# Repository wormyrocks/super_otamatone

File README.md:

# super_otamatone

Because the world needs a better Otamatone.

In order to set up build environment, you must have three .mk files from the Arduino Makefile repository in arduino/build_scripts

Teensy.mk
Common.mk
Arduino.mk

https://github.com/sudar/Arduino-Makefile

Running setup.sh in that directory should download them automatically.
You also need the Arduino application and Teensyduino, as well as the libraries specified in the Makefile.

This library uses my fork of the arduino-menusystem library, which can be found here.
https://github.com/wormyrocks/arduino-menusystem

It is included as a submodule.

'upload' script automates compilation, upload, and opening the serial monitor.

The last two require the tyc program. Find binaries here. https://github.com/Koromix/ty/releases
tyc should also be in /arduino/otamatone.

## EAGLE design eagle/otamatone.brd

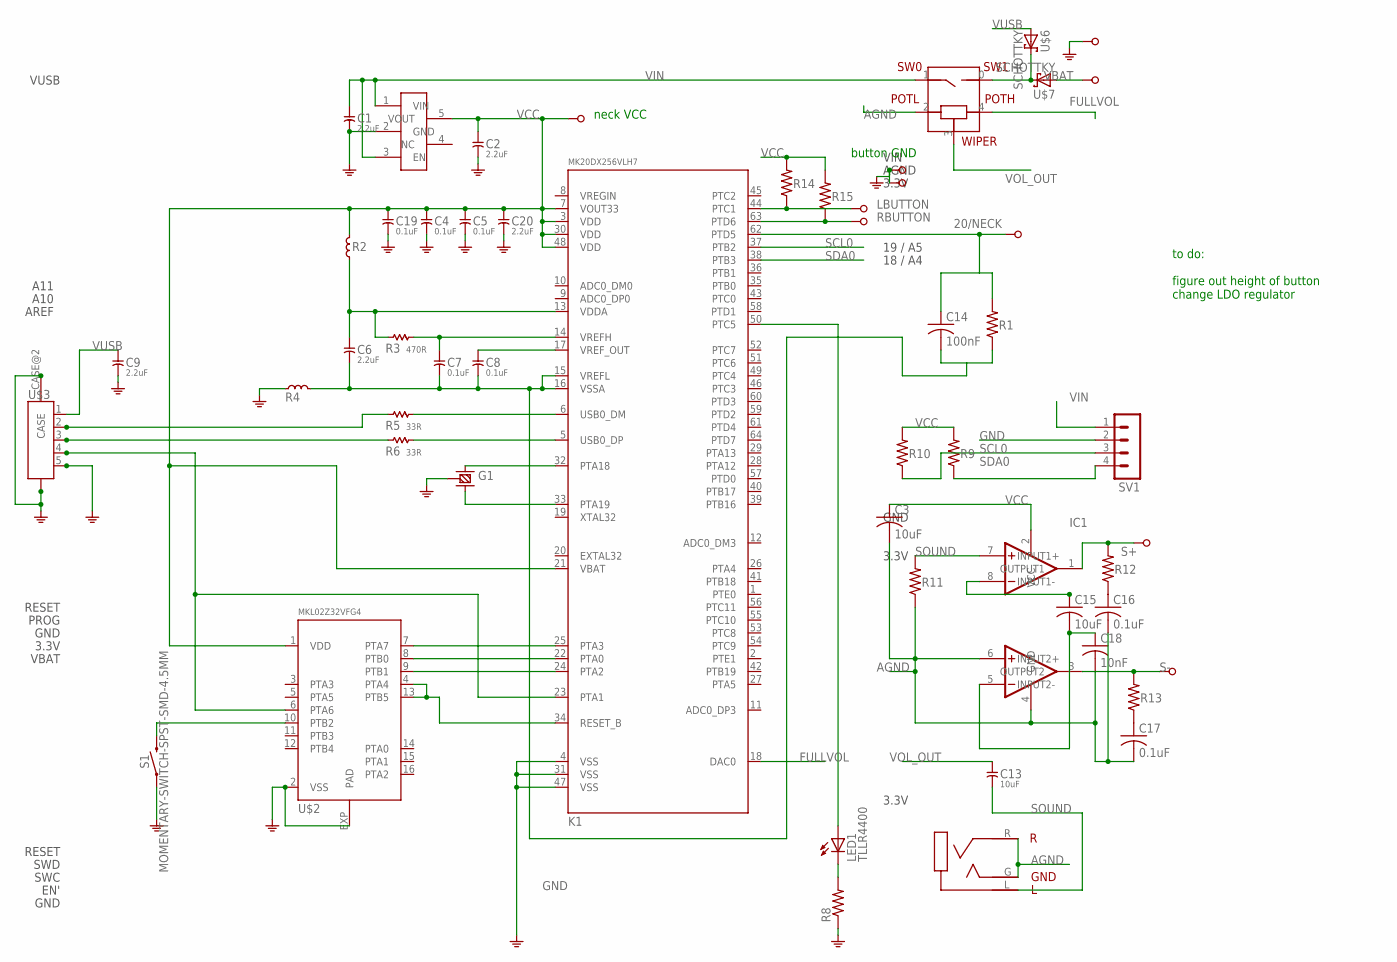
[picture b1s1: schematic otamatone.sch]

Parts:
B+: PIN; PTH_39MIL
B-: PIN; PTH_39MIL
C1, C2, C6, C9, C20: 2.2uF; C0603
C3, C13, C15: 10uF; C0603
C4, C5, C7, C8, C19: 0.1uF; C0402
C14: 100nF; C0402
C16, C17: 0.1uF; C0603
C18: 10nF; C0603
G1: CRYSTAL-; CRYS
IC1: TDA2822MSOP8; SOP8
K1: MK20DX256VLH7; LQFP64-05
LED1: TLLR4400; LED3MM
R1: 62K; R0402
R2, R4: FERRITE; L0603
R3: 470R; R0402
R5, R6: 33R; R0402
R8: R-US_R0603; R0603
R9, R10, R14, R15: 10K; R0402
R11: 10K; R0603
R12, R13: 4.7; R0603
S1: MOMENTARY-SWITCH-SPST-SMD-4.5MM; TACTILE_SWITCH_SMD_4.5MM
S+: PINSMT; SMD
S-: PINSMT; SMD
SV1: MA04-1
SX1, SX2, SX3, SX4: PIN; PTH_39MIL
U$1: P170S; 5PIN_POT
U$2: MKL02Z32VFG4; QFN16
U$3: VERT_USB; TALL_BOI
U$4: VERT_JACK; AUDIOJACK
U$5: AP2112K; SOT25
U$6, U$7: SCHOTTKY; LED-0805
Z+: PINSMT; SMD
Z-: PINSMT; SMD

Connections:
20/NECK: C14.1, K1.62 (PTD5), R1.2, Z-.P$1
AGND: C3.2, C6.2, C7.2, C8.2, C14.2, C16.2, C17.2, C18.2, IC1.4 (GND), IC1.6 (INPUT2+), K1.15 (VREFL), K1.16 (VSSA), R1.1, R4.2, R11.1, U$1.2 (POTL), U$4.G (GND), U$4.R
FULLVOL: K1.18 (DAC0), U$1.4 (POTH)
GND: B-.1, C1.2, C2.2, C4.2, C5.2, C9.2, C19.2, C20.2, G1.P$1 (GND), G1.P$4 (GND), K1.4 (VSS), K1.31 (VSS), K1.47 (VSS), R4.1, R8.1, S1.2 (1), S1.3 (1), SV1.2, SX1.1, SX3.1, U$2.2 (VSS), U$2.EXP (PAD), U$3.5, U$3.CASE, U$3.CASE@2 (CASE), U$5.2 (GND)
LBUTTON: K1.44 (PTC1), R14.1, SX2.1
unnamed: U$1.0 (SW1), U$6.- (C), U$7.- (C)
unnamed: K1.22 (PTA0), U$2.8 (PTB0)
unnamed: K1.24 (PTA2), U$2.9 (PTB1)
unnamed: G1.P$2 (1), K1.32 (PTA18)
unnamed: G1.P$3 (2), K1.33 (PTA19)
unnamed: C15.1, IC1.8 (INPUT1-)
unnamed: K1.25 (PTA3), U$2.7 (PTA7)
unnamed: S1.1 (2), S1.4 (2), U$2.10 (PTB2)
unnamed: C8.1, K1.17 (VREF_OUT)
unnamed: K1.34 (RESET_B), U$2.4 (PTA4), U$2.13 (PTB5)
unnamed: C7.1, K1.14 (VREFH), R3.2
unnamed: C6.1, K1.13 (VDDA), R2.1, R3.1
unnamed: C16.1, R12.1
unnamed: K1.23 (PTA1), U$2.6 (PTA6), U$3.4
unnamed: C17.1, R13.1
unnamed: C15.2, C18.1, IC1.5 (INPUT2-)
unnamed: K1.50 (PTC5), LED1.A
unnamed: LED1.K (C), R8.2
RBUTTON: K1.63 (PTD6), R15.1, SX4.1
S+: IC1.1 (OUTPUT1), R12.2, S+.P$1
S-: IC1.3 (OUTPUT2), R13.2, S-.P$1
SCL0: K1.37 (PTB2), R10.1, SV1.3
SDA0: K1.38 (PTB3), R9.1, SV1.4
SOUND: C13.2, IC1.7 (INPUT1+), R11.2, U$4.L
USB0_DM: K1.6 (USB0_DM), R5.2
USB0_DP: K1.5 (USB0_DP), R6.2
USB_M: R5.1, U$3.2
USB_P: R6.1, U$3.3
VBAT: B+.1, U$7.+ (A)
VCC: C2.1, C3.1, C4.1, C5.1, C19.1, C20.1, IC1.2 (VCC), K1.3 (VDD), K1.7 (VOUT33), K1.21 (VBAT), K1.30 (VDD), K1.48 (VDD), R2.2, R9.2, R10.2, R14.2, R15.2, U$2.1 (VDD), U$5.5 (VOUT), Z+.P$1
VIN: C1.1, SV1.1, U$1.1 (SW0), U$5.1 (VIN), U$5.3 (EN)
VOL_OUT: C13.1, U$1.3 (WIPER)
VUSB: C9.1, U$3.1, U$6.+ (A)

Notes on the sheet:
VIN
AGND
3.3V
19 / A5
18 / A4
GND
VBAT
RESET
PROG
A11
A10
AREF
VUSB
SWD
SWC
EN'
to do: figure out height of button change LDO regulator
neck VCC
button GND

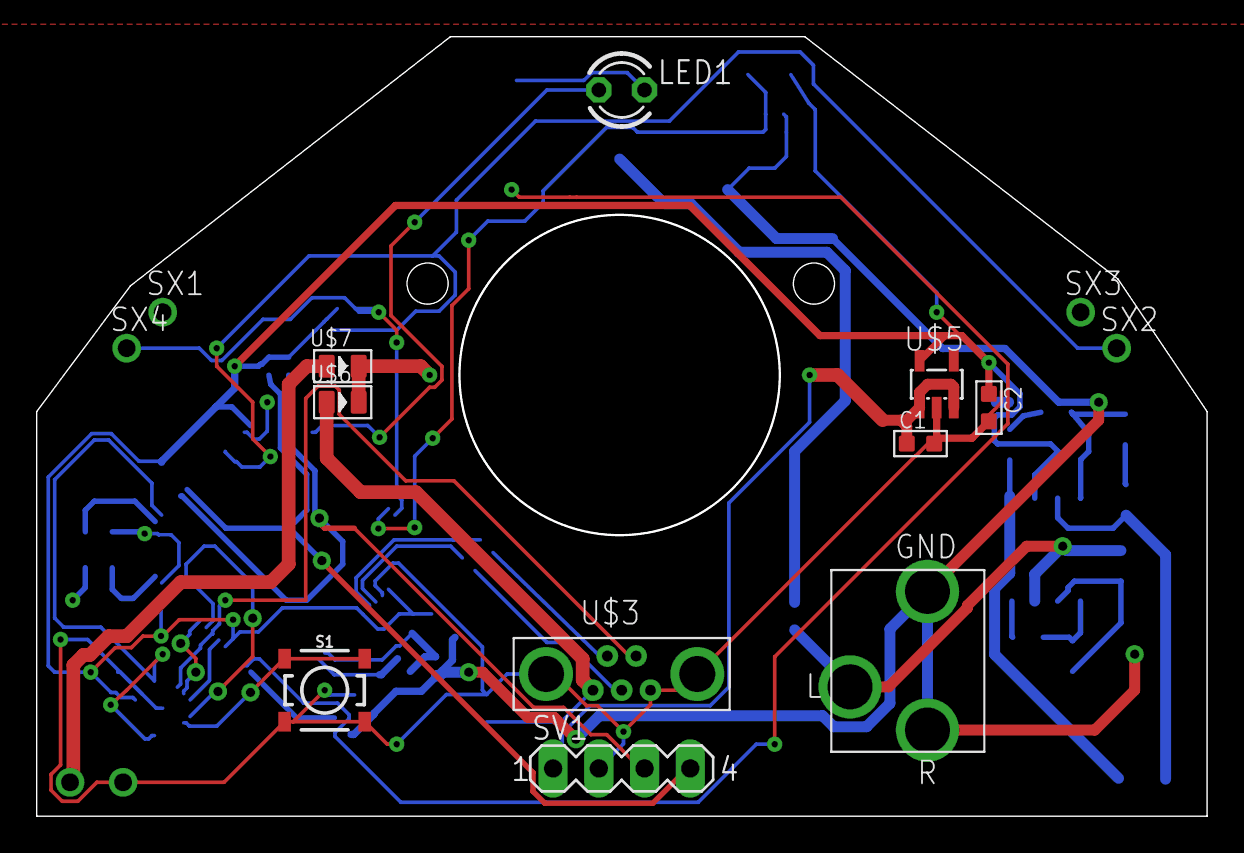
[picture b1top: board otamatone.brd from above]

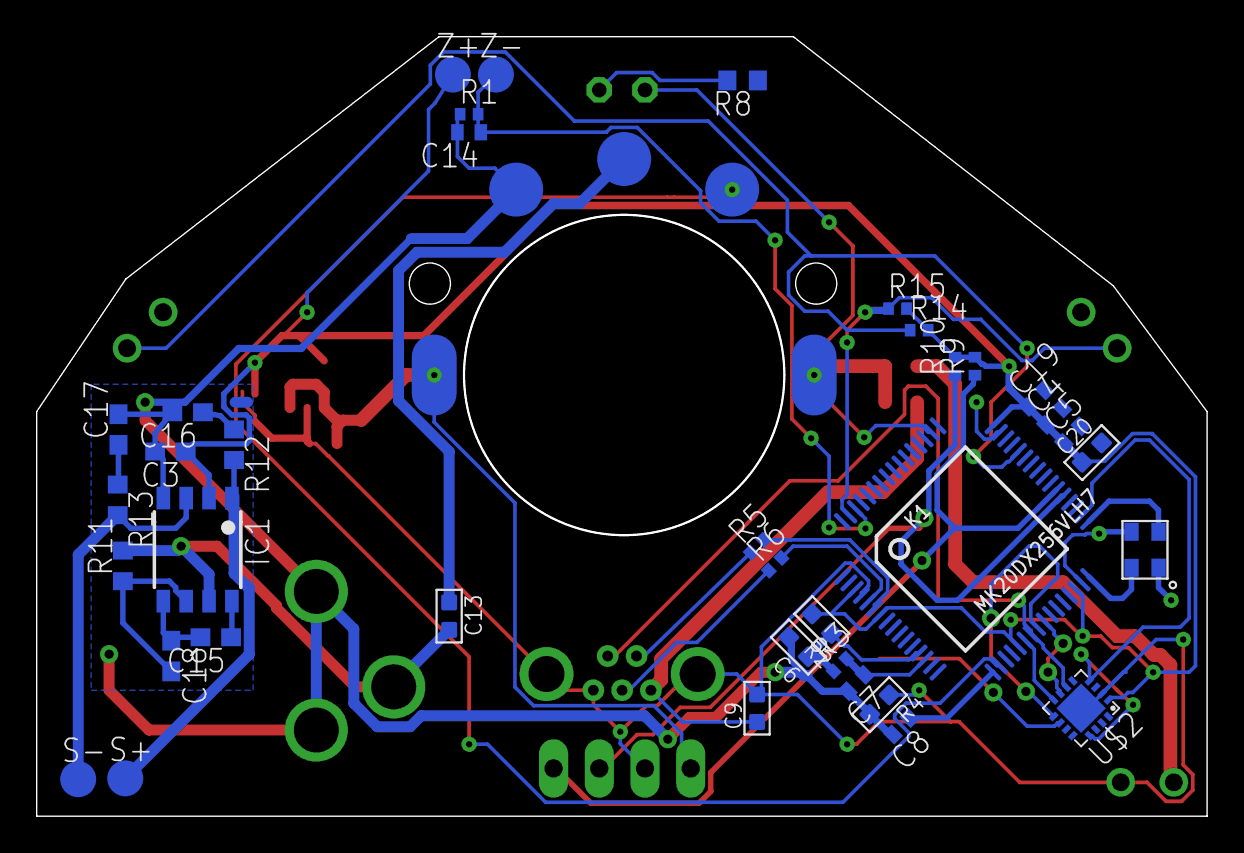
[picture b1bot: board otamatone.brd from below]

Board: 2 copper layers, 65.0 x 43.3 mm, 54 parts (38 on the bottom side), 38 nets.

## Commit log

2016-10-25 Initial commit.
2016-10-25 renamed file
2016-10-25 cleaned up code
2016-10-25 added gitignore
2016-10-25 Removed DS_Store.
2016-10-26 fixed bugs
2016-10-29 added display code and adjusted otamatone scaling stuff
2016-10-29 added synth files for good
2016-10-29 removed gross excel formula
2016-10-30 switched to interrupts over polling
2016-10-30 fixxed algo
2016-10-31 added wavetable
2016-10-31 fixed wavetable code
2016-11-07 undid synth table
2016-11-13 added octave switch functionality
2016-11-13 Add line in functionality.
2016-11-14 Begin working on menu framework.
2016-11-14 added 'oto tune' (disabled by default)
2016-11-14 added sample code for navigating menus on-device
2016-11-14 initialize display in edit mode
2016-11-14 Remove extraneous menu sample code.
2016-11-14 Fixed minor bug.
2016-11-14 Did my forward declarations properly.
2016-11-14 Convert int flags to bitwise flags. Untested.
2016-11-15 Add (shiity) digital volume control.
2016-11-15 added oto tune and variable adc res
2016-11-15 compartmentalized arduino code into multiple files
2016-11-16 Add build directory. Compartmentalize into files. Not sure if this build works.
2016-11-17 added boot images
2016-11-23 Added submodule.
2016-11-28 Add fritzing interposer design (shudder).
2016-11-28 Small updates to interposer pcb.
2016-11-28 Incremental update to breakout layout.
2016-11-29 Probably functional breakout pcb.
2016-11-29 Finished top half part labels.
2016-11-29 Minor tweaks.
2016-11-30 Added top and bottom silkscreens. This version of the breakout board was sent to OSHPark.
2016-11-30 Clean up, update readme, add submodule to proper location.
2016-12-02 Include new menu system. (Not tested on device, but compiles.)
2016-12-05 Updated pin assignments for PCB.
2016-12-28 Move synth to its own class. Clean up bad code.
2016-12-28 Cleaned up old files.
2016-12-28 Add small hole to board file.
2016-12-28 Updated readme, included setup script for build
2018-02-14 Overhauled file structure, began work on new PCB design
2018-02-15 Incremental updates to schematic and firmware
2018-02-21 Updated schematics
2018-02-28 sync changes
2018-02-28 Updated gitignore and board contents
    unrouted components are now drc compliant, through hole components have been place
2018-03-01 started laying out pcb
2018-03-02 first pass at routing board
2018-03-08 Repaired some code in the menu system
2018-03-13 bug fixes to menu system, still not usable

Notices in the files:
parts and their libraries:
SparkFun-Switches: Licensing: Creative Commons ShareAlike 4.0 International - https://creativecommons.org/licenses/by-sa/4.0
